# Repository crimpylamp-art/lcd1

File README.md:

View this project on [CADLAB.io](https://cadlab.io/project/30531). 

# lcd1

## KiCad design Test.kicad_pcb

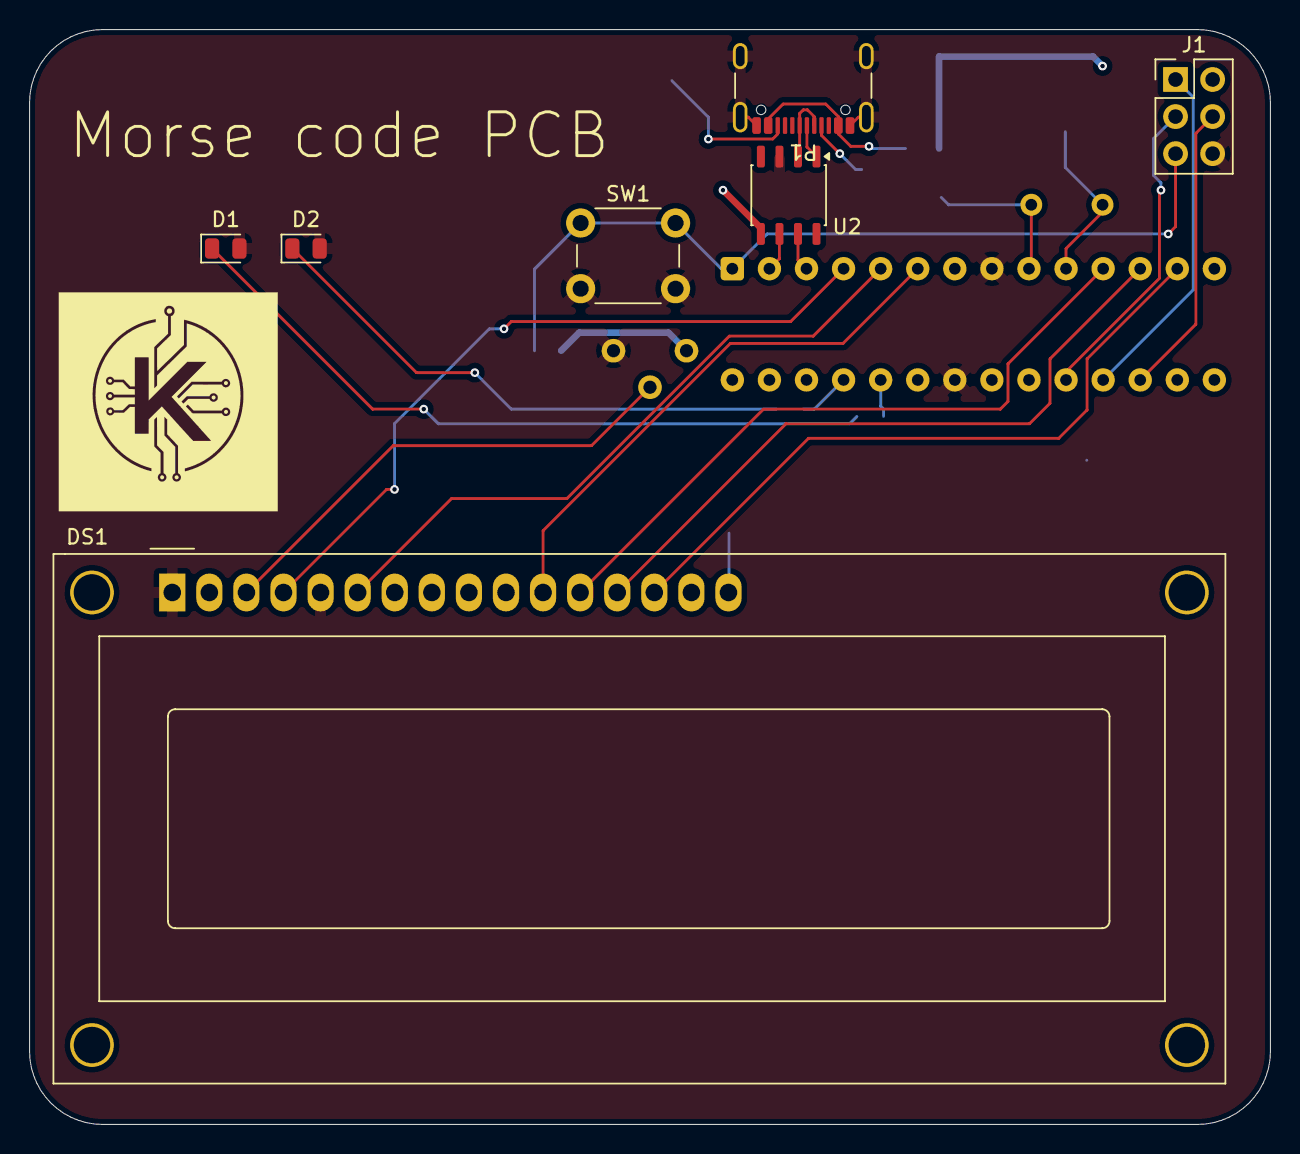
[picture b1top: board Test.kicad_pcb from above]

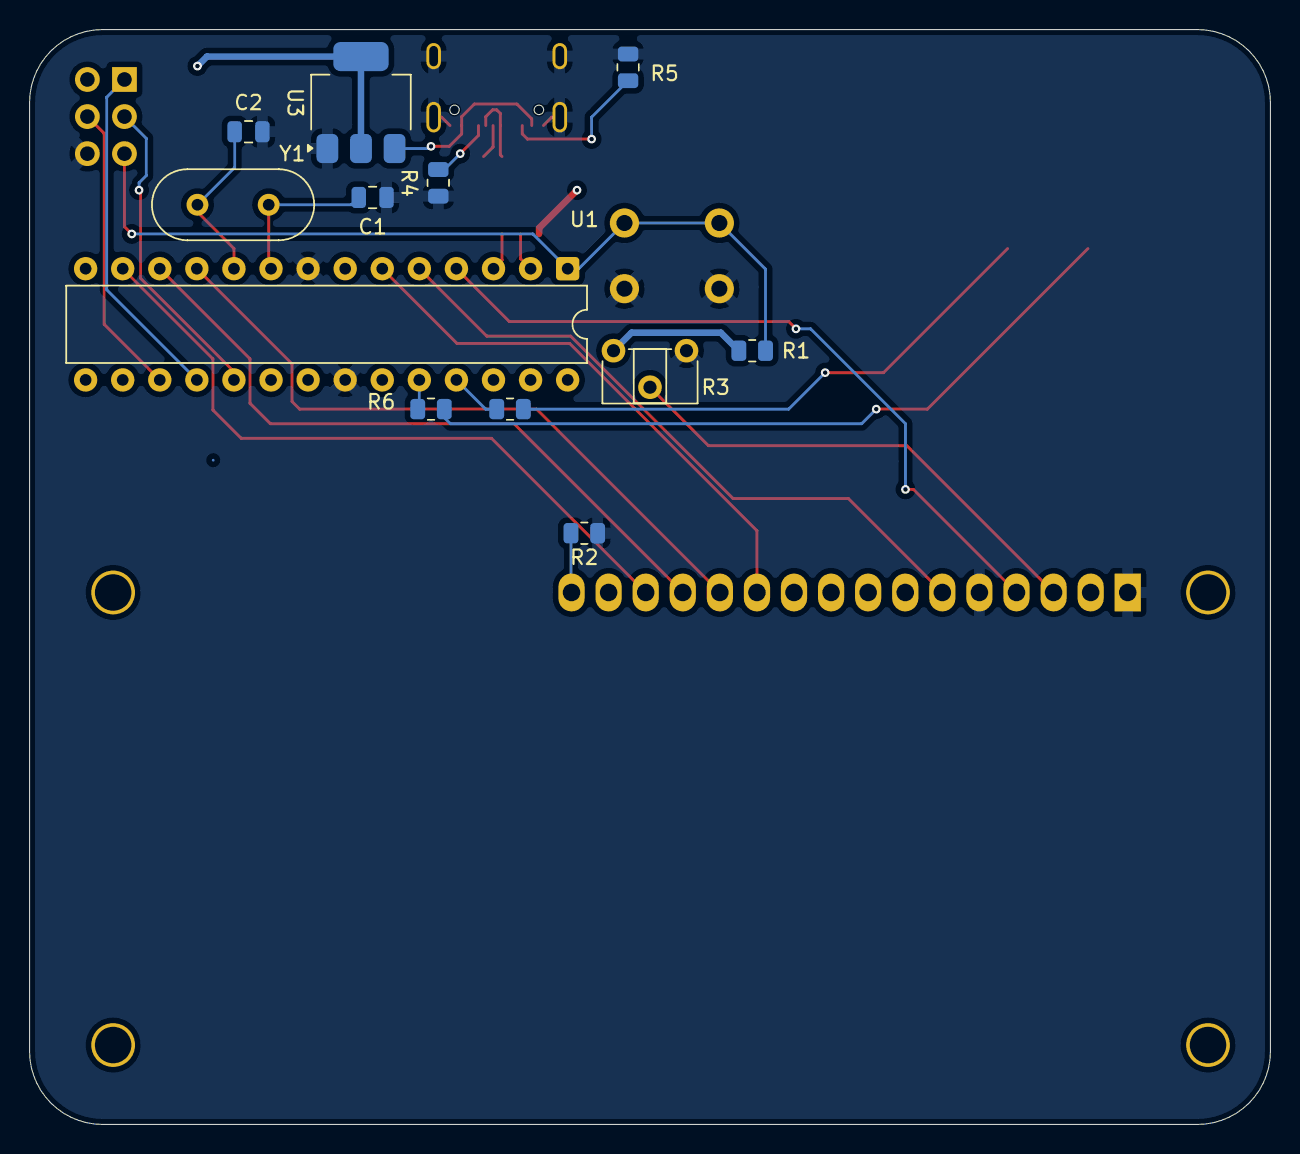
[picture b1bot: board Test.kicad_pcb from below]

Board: 4 copper layers, 85.0 x 75.0 mm, 19 parts (12 on the bottom side), 27 nets.

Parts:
C1, C2: 22pF; C_0805_2012Metric
D1: LED1; LED_0805_2012Metric
D2: LED2; LED_0805_2012Metric
DS1: WC1602A
J1: AVR-ISP-6; PinHeader_2x03_P2.54mm_Vertical
P1: USB_C_Receptacle_USB2.0; USB_C_Receptacle_GCT_USB4105-xx-A_16P_TopMnt_Horizontal
R1: 10k; R_0805_2012Metric
R2: 220Ω; R_0805_2012Metric
R3: 10k; Potentiometer_ACP_CA6-H2,5_Horizontal
R4, R5: 5.1k; R_0805_2012Metric
R6, R7: 220; R_0805_2012Metric
SW1: SW_Push; SW_PUSH_6mm
U1: ATmega328P-P; DIP-28_W7.62mm
U2: CH340N; JEITA_SOIC-8_3.9x4.9mm_P1.27mm
U3: AMS1117; SOT-223-3_TabPin2
Y1: Crystal; Crystal_HC49-U_Vertical

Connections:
+5V: DS1.2 (VDD), J1.2 (VCC), R1.1, R3.3, U1.7 (VCC), U1.20 (AVCC), U2.5 (VCC), U3.2 (VO)
CH340N_RX: U1.3 (PD1), U2.7 (RXD)
CH340N_TX: U1.2 (PD0), U2.6 (TXD)
GND: C1.2, C2.1, D1.2 (A), D2.2 (A), DS1.1 (VSS), DS1.5 (R/W), J1.6 (GND), P1.A1 (GND), P1.A12 (GND), P1.B1 (GND), P1.B12 (GND), P1.SH (SHIELD), R2.1, R3.1, R4.2, R5.2, SW1.2, U1.8 (GND), U1.22 (GND), U2.3 (GND), U3.1 (ADJ)
Miso: J1.1 (MISO), U1.18 (PB4)
Mosi: J1.4 (MOSI), U1.17 (PB3)
unnamed: D1.1 (K), R6.2
unnamed: D2.1 (K), R7.2
unnamed: DS1.11 (D4), U1.6 (PD4)
unnamed: DS1.12 (D5), U1.11 (PD5)
unnamed: DS1.13 (D6), U1.12 (PD6)
unnamed: DS1.14 (D7), U1.13 (PD7)
unnamed: DS1.6 (E), U1.5 (PD3)
unnamed: DS1.16 (LED(-)), R2.2
unnamed: DS1.4 (RS), U1.4 (PD2)
unnamed: DS1.3 (VO), R3.2
unnamed: P1.A5 (CC1), R4.1
unnamed: P1.B5 (CC2), R5.1
unnamed: C1.1, U1.9 (XTAL1/PB6), Y1.1
unnamed: C2.2, U1.10 (XTAL2/PB7), Y1.2
unnamed: P1.A4 (VBUS), P1.A9 (VBUS), P1.B4 (VBUS), P1.B9 (VBUS), U3.3 (VI)
PC1: R6.1, U1.24 (PC1)
PC2: R7.1, U1.25 (PC2)
RST: J1.5 (~RST), R1.2, SW1.1, U1.1 (~RESET/PC6)
SCK: J1.3 (SCK), U1.19 (PB5)
USB_C D+: P1.A6 (D+), P1.B6 (D+), U2.1 (UD+)
USB_C D-: P1.A7 (D-), P1.B7 (D-), U2.2 (UD-)
